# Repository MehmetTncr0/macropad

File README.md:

# 🎹 12-Key RP2040 Macropad (v1.0)

A 12-key (3x4 layout) mechanical macropad powered by the **Raspberry Pi Pico**, featuring an OLED display, rotary encoder, and an analog potentiometer. 

Designed for macro execution, volume control, layer switching, and media controls.

---

## 🛠️ Hardware

* **Brain:** Raspberry Pi Pico (RP2040)
* **Keys:** 12x Mechanical Switches (3x4 Matrix)
* **Display:** 0.96" SSD1306 OLED (I2C)
* **Controls:** 
  * 1x EC11 Rotary Encoder (with push button)
  * 1x 10k Potentiometer (analog input)
* **PCB Specs:** 2-Layer FR4 | 1.6mm thickness | Dual-sided GND plane

## 🛠️ Features
* Volume level control via potantiometer
* Output device control via potantiometer switch
* All sound settings on one component
-------------------------------------
* Refeaturable 12 Mechanical Switches with rgb lights
* Switch1 => Changes RGB mode
* Switch2 => Changes RGB color
* Switch3 => Turn on/off the microphone
* Switch4 => Alt + Tab Hotkey
* Switch5 => Windows + Shift + S Hotkey
* Switch6 => " Hotkey because I don't have that in my own keyboard
* Switch7 => to continue or pause the song/video
* Switch8 => turns volume to zero instantly
* switch9 => opens youtube
* switch10 => opens google
* switch11 => runs cmd
* switch12 => turns off the light

----------------------------------

## 📦 Bill of Materials (BOM)

| Component | Reference | Quantity | Description |
| :--- | :--- | :--- | :--- |
| Raspberry Pi Pico | U1 | 1 | Microcontroller Board |
| 0.96" I2C OLED | DISP1 | 1 | 128x64 Display |
| Mechanical Switches | SW1–SW12 | 12 | Key Switches (3x4 layout) |
| Rotary Encoder | ROT1 | 1 | EC11 Encoder with Switch |
| Potentiometer | RV1 | 1 | 10k Linear Potentiometer |

---

## 🔧 Design & Status

* **KiCad Routing:** 0 DRC Errors / 0 DRC Warnings.
* **Trace Widths:** 0.2mm for signals, 0.4–0.5mm for power lines.
* **Firmware Target:** KMK Firmware / CircuitPython.
*

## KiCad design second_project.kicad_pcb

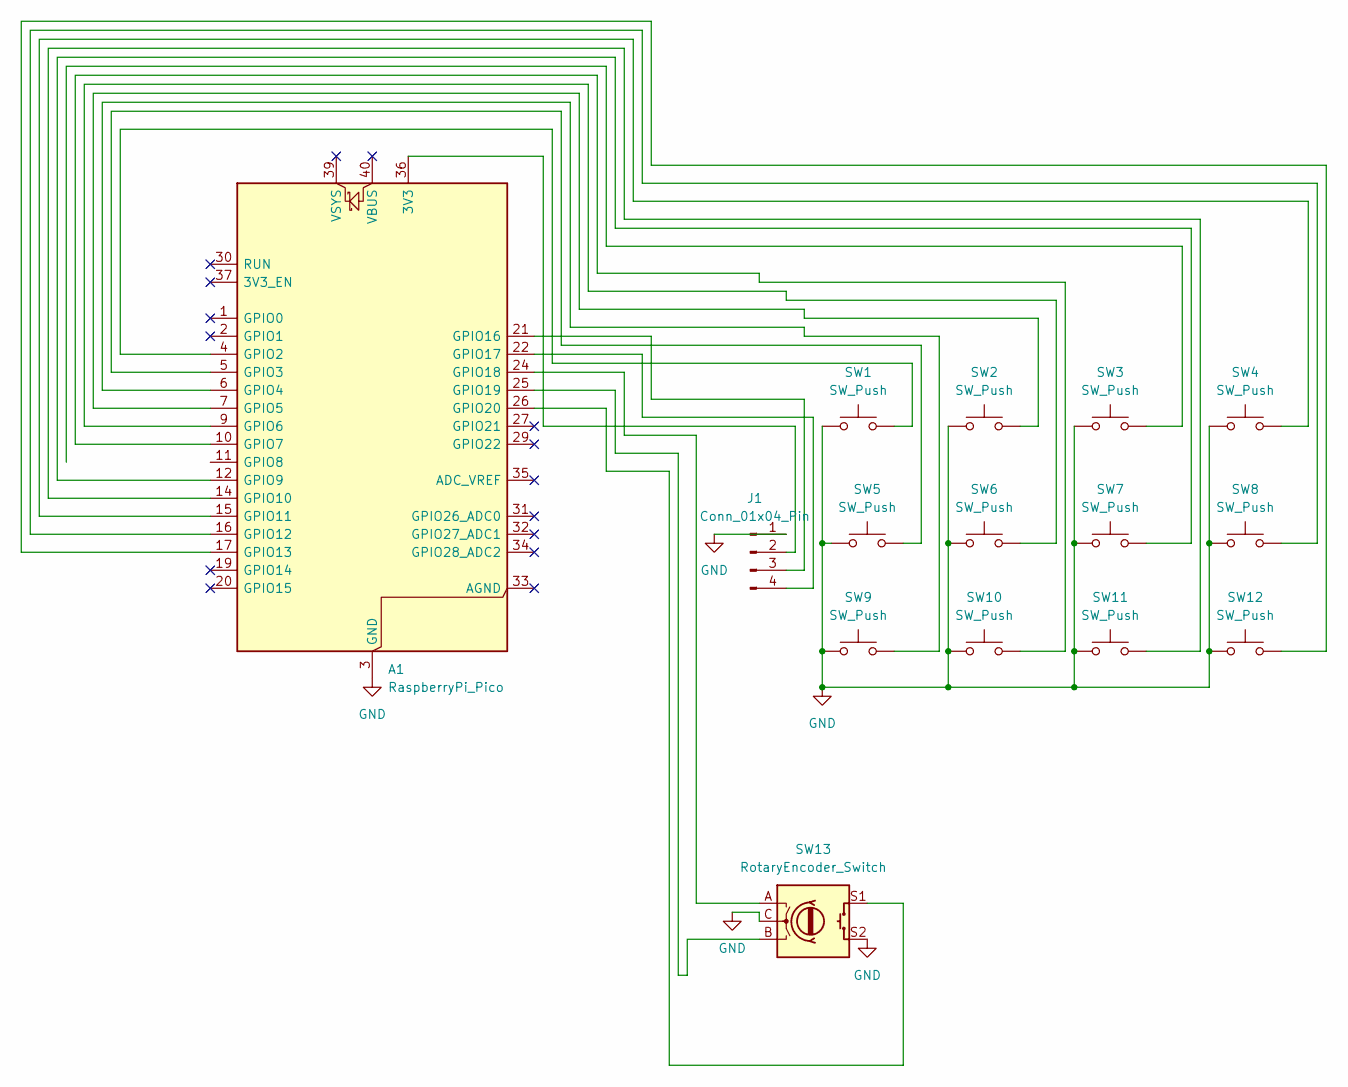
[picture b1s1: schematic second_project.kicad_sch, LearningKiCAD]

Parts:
A1: RaspberryPi_Pico; RaspberryPi_Pico_Common_Unspecified
J1: Conn_01x04_Pin; PinHeader_1x04_P2.54mm_Vertical
SW1, SW2, SW3, SW4, SW5, SW6, SW7, SW8, SW9, SW10, SW11, SW12: SW_Push; SW_Cherry_MX_1.00u_Plate
SW13: RotaryEncoder_Switch; RotaryEncoder_Alps_EC12E-Switch_Vertical_H20mm

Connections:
GND: A1.3 (GND), A1.8 (GND), A1.13 (GND), A1.18 (GND), A1.23 (GND), A1.28 (GND), A1.38 (GND), J1.1, SW1.1, SW2.1, SW3.1, SW4.1, SW5.1, SW6.1, SW7.1, SW8.1, SW9.1, SW10.1, SW11.1, SW12.1, SW13.C, SW13.S2
unnamed: A1.36 (3V3), J1.2
unnamed: A1.4 (GPIO2), SW1.2
unnamed: A1.5 (GPIO3), SW5.2
unnamed: A1.6 (GPIO4), SW9.2
unnamed: A1.7 (GPIO5), SW2.2
unnamed: A1.9 (GPIO6), SW6.2
unnamed: A1.10 (GPIO7), SW10.2
unnamed: A1.11 (GPIO8), SW3.2
unnamed: A1.12 (GPIO9), SW7.2
unnamed: A1.14 (GPIO10), SW11.2
unnamed: A1.15 (GPIO11), SW4.2
unnamed: A1.16 (GPIO12), SW8.2
unnamed: A1.17 (GPIO13), SW12.2
unnamed: A1.21 (GPIO16), J1.3
unnamed: A1.22 (GPIO17), J1.4
unnamed: A1.24 (GPIO18), SW13.A
unnamed: A1.25 (GPIO19), SW13.B
unnamed: A1.26 (GPIO20), SW13.S1

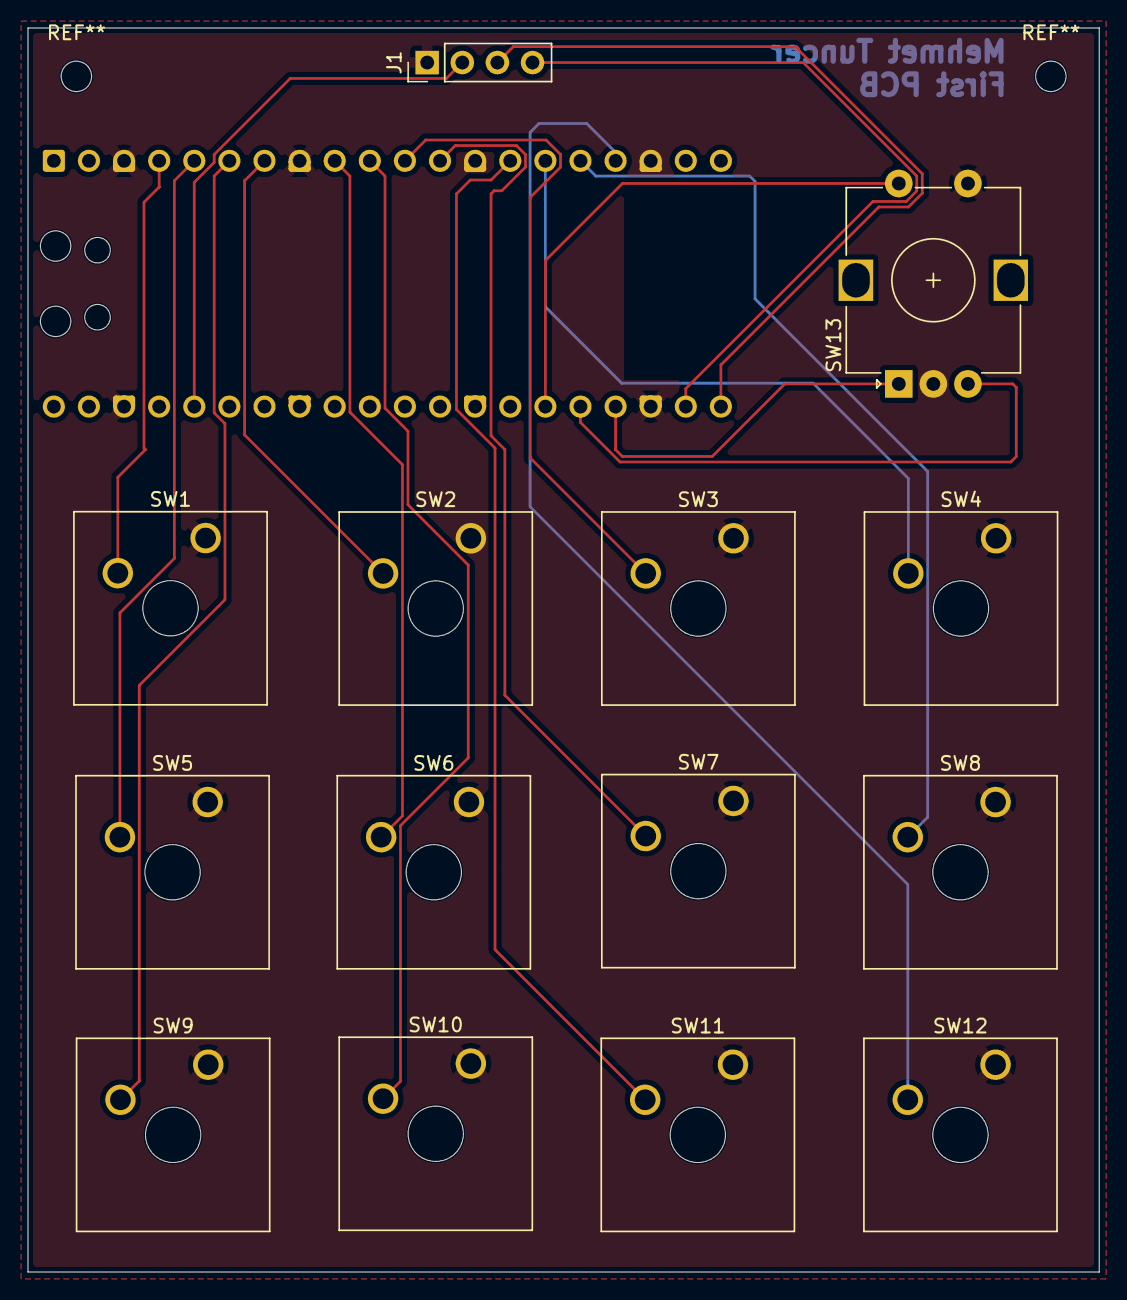
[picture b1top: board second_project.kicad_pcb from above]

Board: 2 copper layers, 77.5 x 90.0 mm, 15 parts (1 on the bottom side), 19 nets.
